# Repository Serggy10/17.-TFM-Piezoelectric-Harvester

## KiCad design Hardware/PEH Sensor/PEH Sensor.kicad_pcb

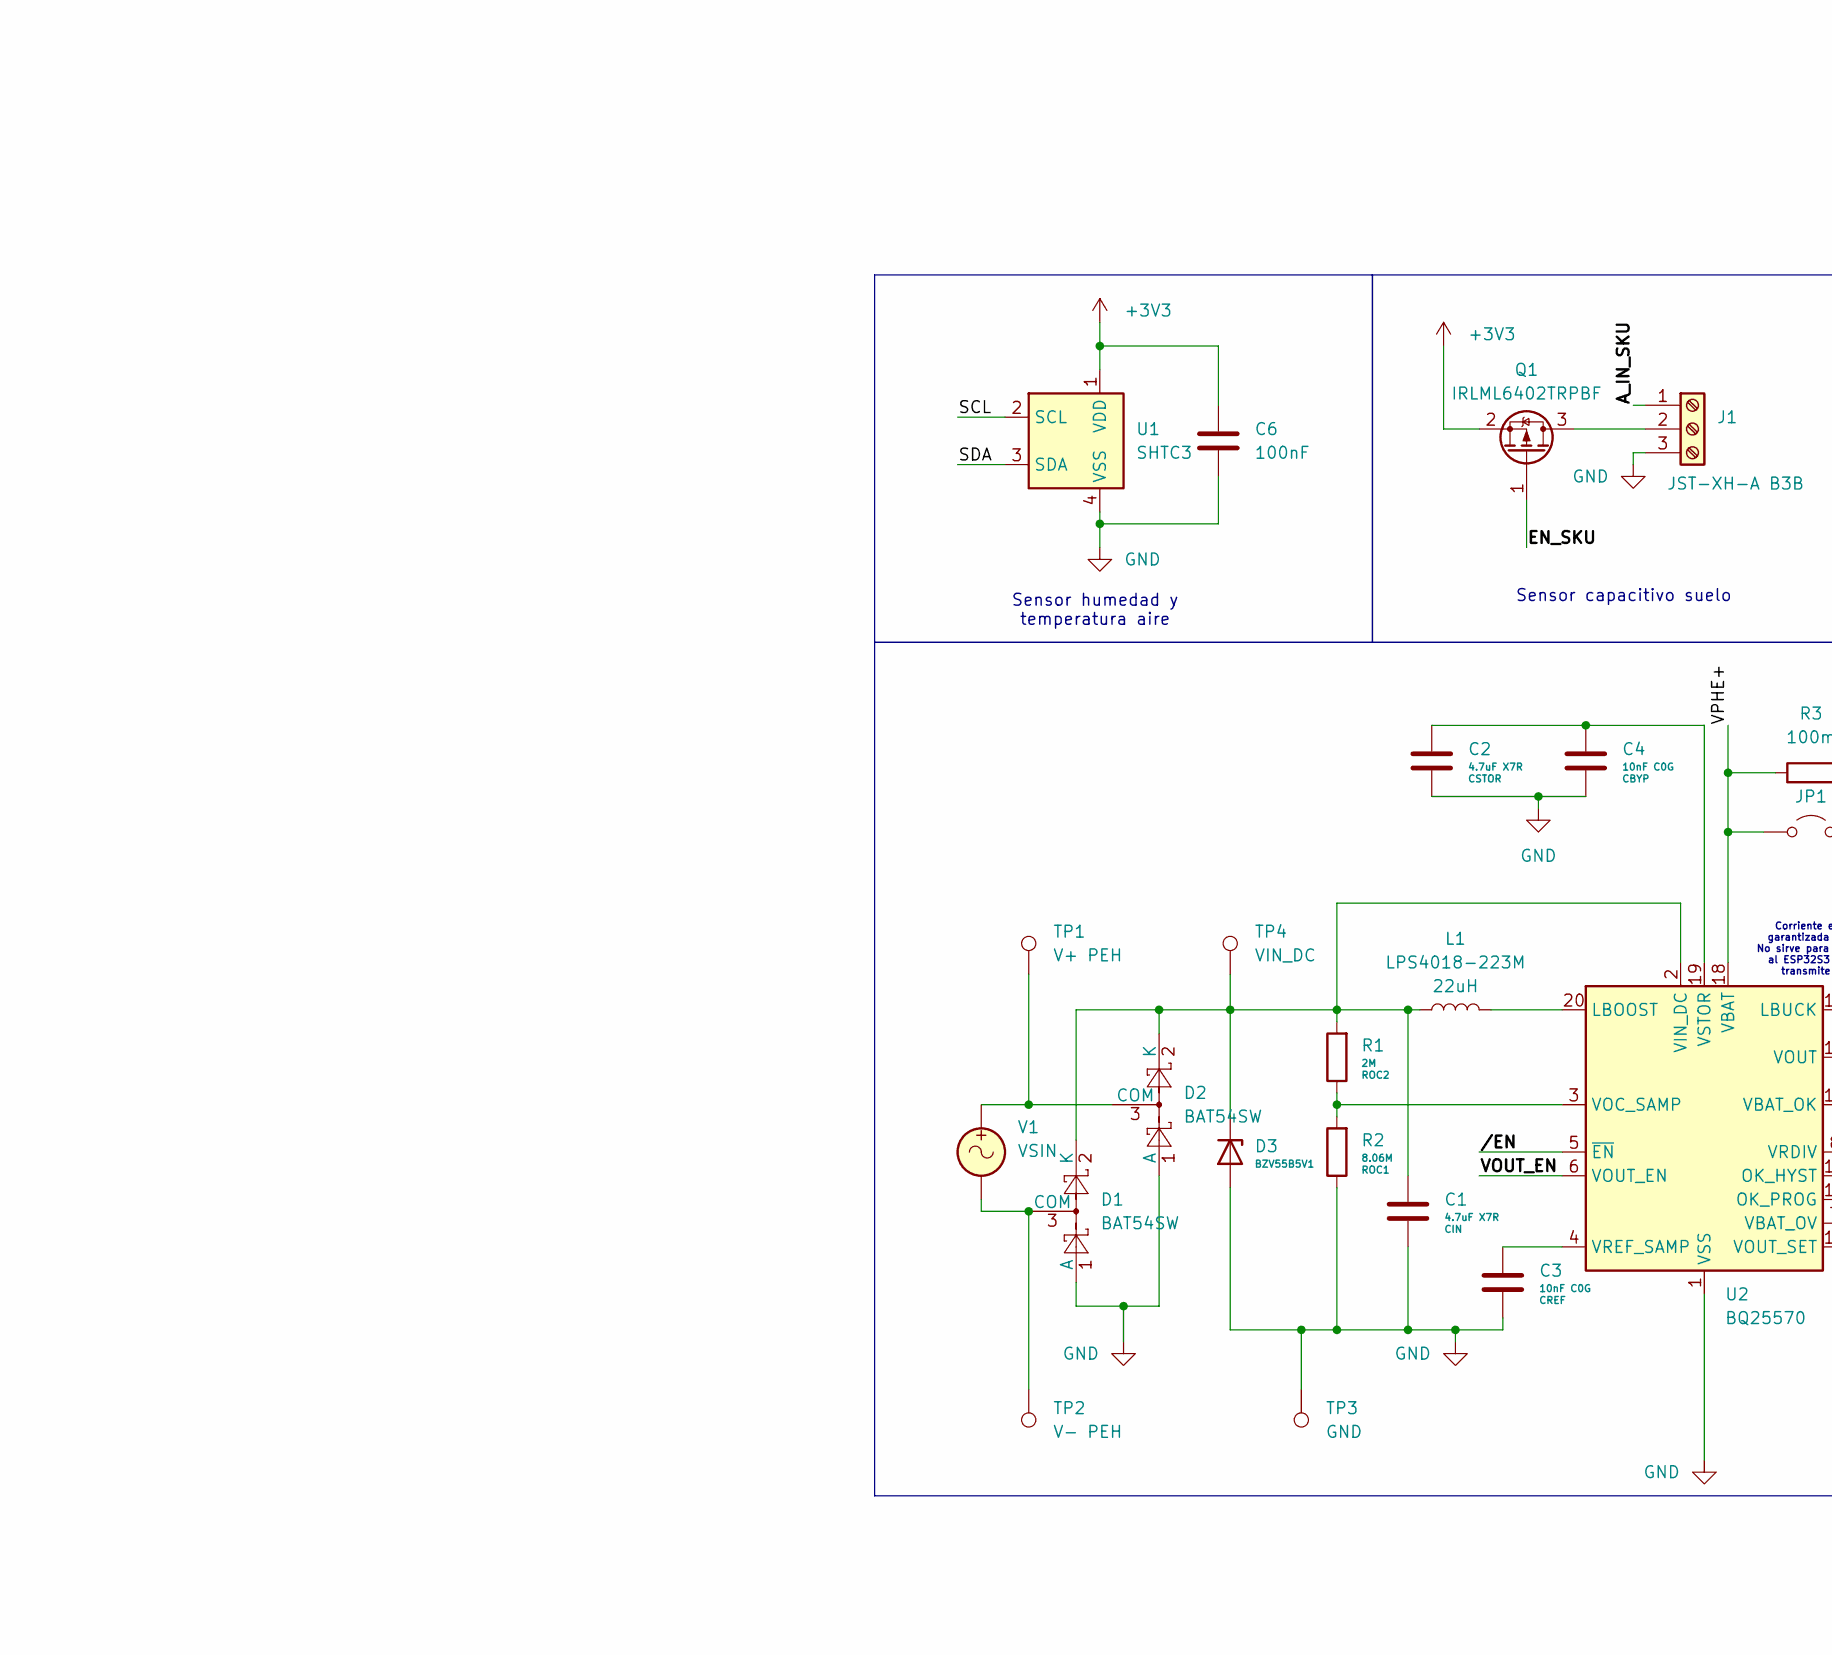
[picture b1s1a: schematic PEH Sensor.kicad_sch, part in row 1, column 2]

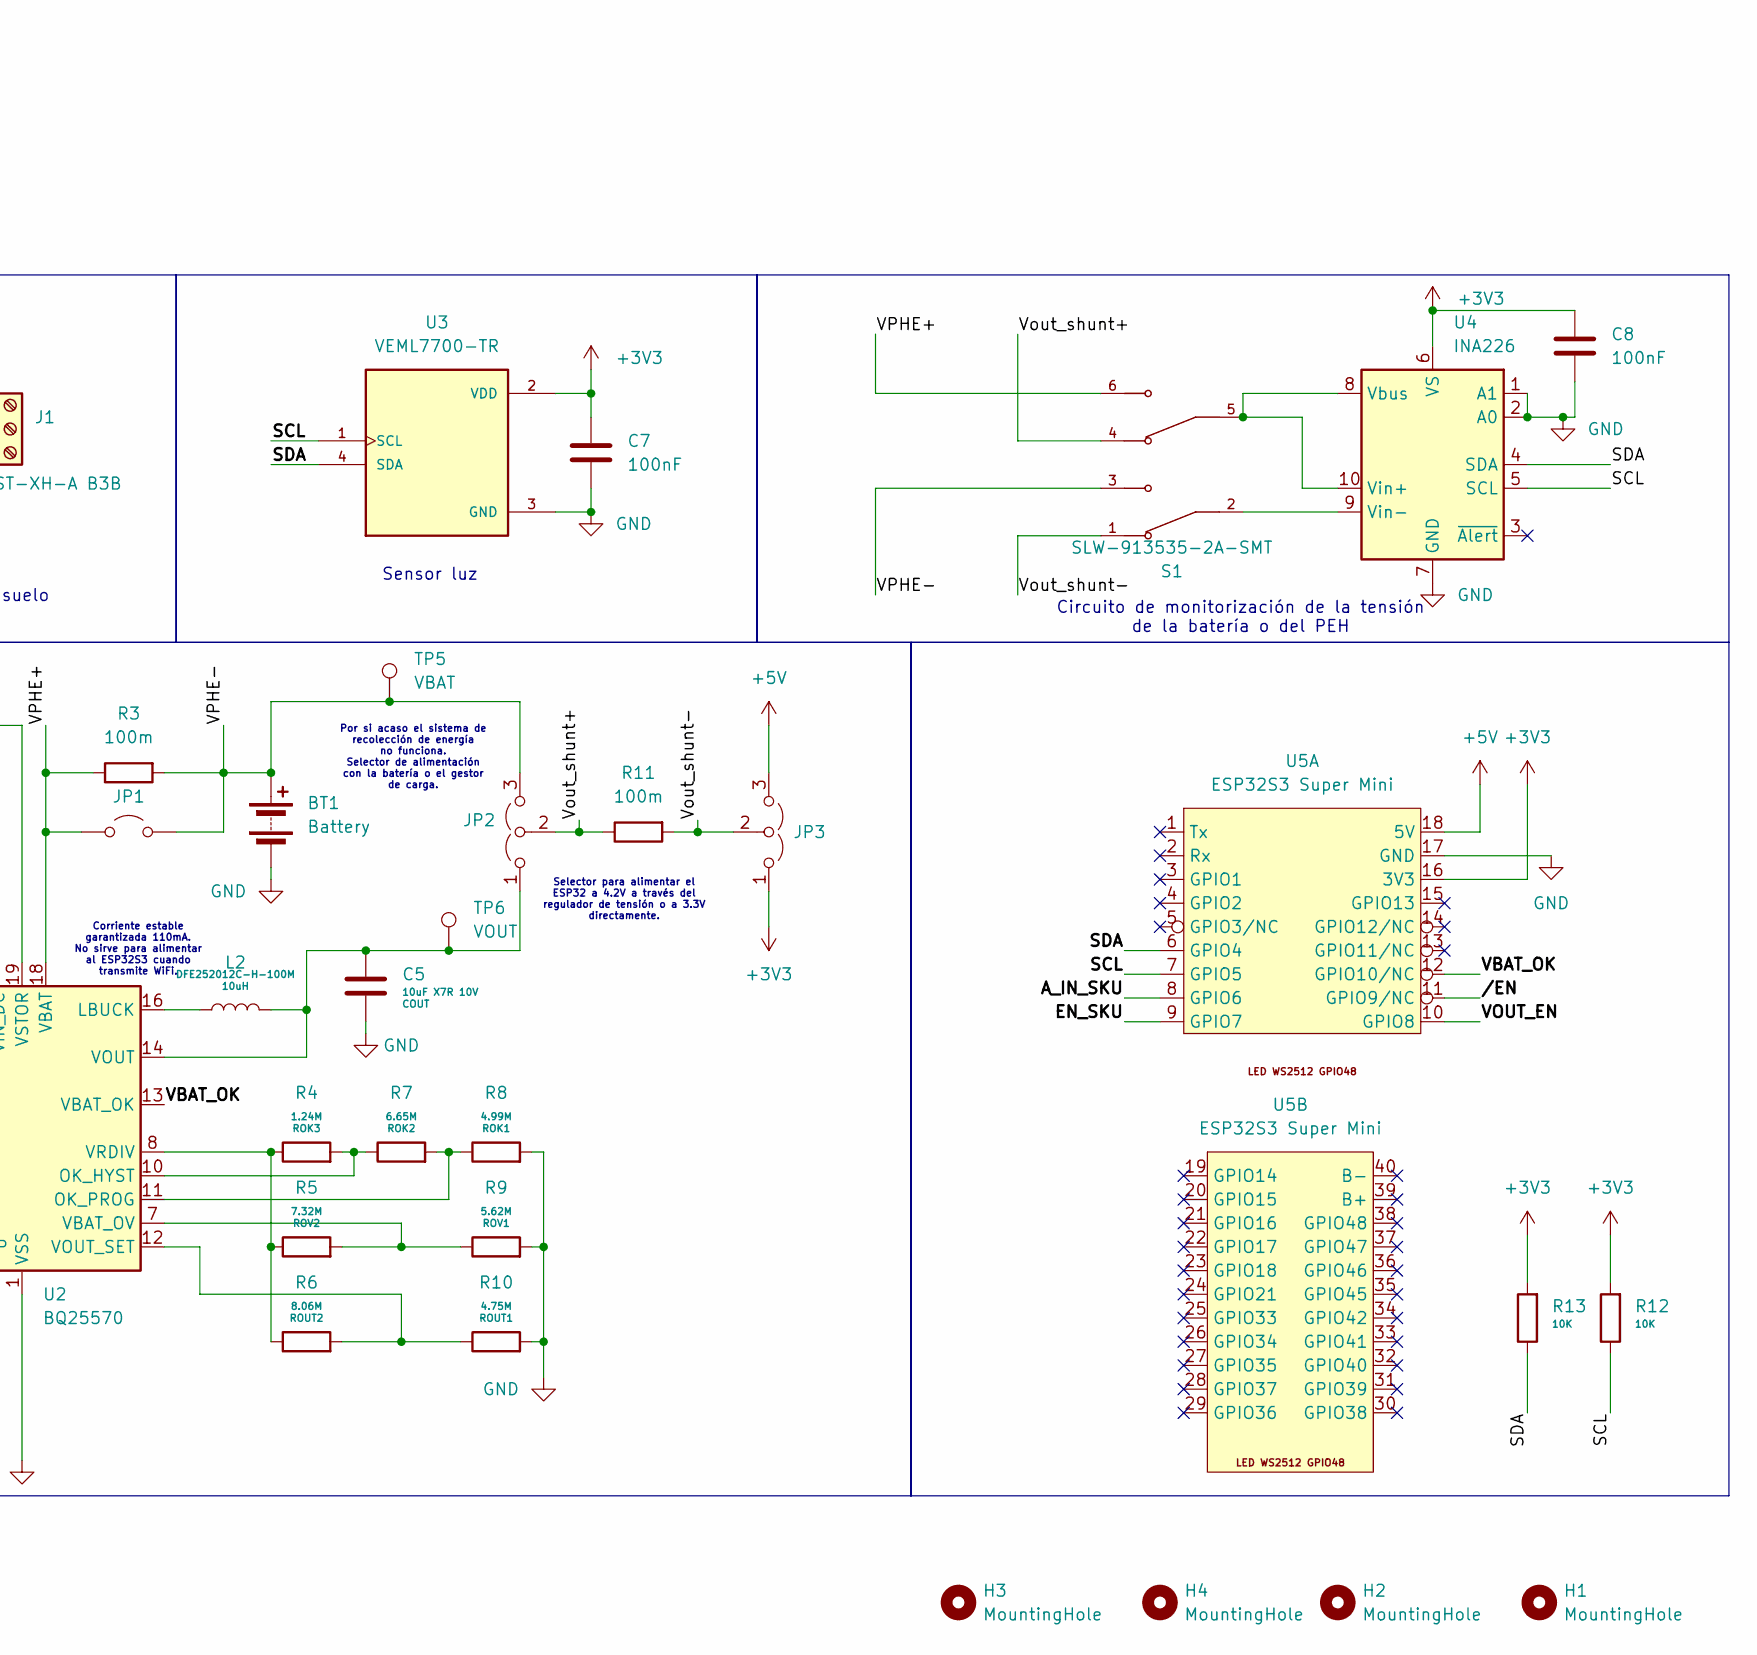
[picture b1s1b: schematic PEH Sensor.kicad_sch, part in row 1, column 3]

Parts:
BT1: Battery; JST_XH_B2B-XH-A_1x02_P2.50mm_Vertical
C1, C2: 4.7uF X7R; C_0805_2012Metric_Pad1.18x1.45mm_HandSolder
C3, C4: 10nF C0G; C_0805_2012Metric_Pad1.18x1.45mm_HandSolder
C5: 10uF X7R 10V; C_0805_2012Metric_Pad1.18x1.45mm_HandSolder
C6, C7, C8: 100nF; C_0805_2012Metric_Pad1.18x1.45mm_HandSolder
D1, D2: BAT54SW; SOT-323_SC-70
D3: BZV55B5V1; D_MiniMELF
H1, H2, H3, H4: MountingHole; MountingHole_3.2mm_M3_DIN965
J1: JST-XH-A B3B; JST_XH_B3B-XH-A_1x03_P2.50mm_Vertical
JP1: Jumper_2_Open; SolderJumper-2_P1.3mm_Open_Pad1.0x1.5mm
JP2, JP3: Jumper_3_Open; SolderJumper-3_P1.3mm_Open_Pad1.0x1.5mm_NumberLabels
L1: LPS4018-223M; L_Coilcraft_LPS4018
L2: DFE252012C-H-100M; L_1008_2520Metric_Pad1.43x2.20mm_HandSolder
Q1: IRLML6402TRPBF; SOT-23
R1: 2M; R_0805_2012Metric_Pad1.20x1.40mm_HandSolder
R2, R6: 8.06M; R_0805_2012Metric_Pad1.20x1.40mm_HandSolder
R3, R11: 100m; R_0805_2012Metric_Pad1.20x1.40mm_HandSolder
R4: 1.24M; R_0805_2012Metric_Pad1.20x1.40mm_HandSolder
R5: 7.32M; R_0805_2012Metric_Pad1.20x1.40mm_HandSolder
R7: 6.65M; R_0805_2012Metric_Pad1.20x1.40mm_HandSolder
R8: 4.99M; R_0805_2012Metric_Pad1.20x1.40mm_HandSolder
R9: 5.62M; R_0805_2012Metric_Pad1.20x1.40mm_HandSolder
R10: 4.75M; R_0805_2012Metric_Pad1.20x1.40mm_HandSolder
R12, R13: 10K; R_0805_2012Metric_Pad1.20x1.40mm_HandSolder
S1: SLW-913535-2A-SMT; SW_SLW-913535-2A-SMT; PARTREV 1.01
TP1: V+ PEH; TestPoint_Loop_D1.80mm_Drill1.0mm_Beaded
TP2: V- PEH; TestPoint_Loop_D1.80mm_Drill1.0mm_Beaded
TP3: GND; TestPoint_Loop_D1.80mm_Drill1.0mm_Beaded
TP4: VIN_DC; TestPoint_Loop_D1.80mm_Drill1.0mm_Beaded
TP5: VBAT; TestPoint_Loop_D1.80mm_Drill1.0mm_Beaded
TP6: VOUT; TestPoint_Loop_D1.80mm_Drill1.0mm_Beaded
U1: SHTC3; Sensirion_DFN-4-1EP_2x2mm_P1mm_EP0.7x1.6mm
U2: BQ25570; QFN-20-1EP_3.5x3.5mm_P0.5mm_EP2x2mm
U3: VEML7700-TR; XDCR_VEML7700-TR; PARTREV 1.6
U4: INA226; VSSOP-10_3x3mm_P0.5mm
U5: ESP32S3 Super Mini; ESP32 super mini
V1: VSIN; JST_XH_B2B-XH-A_1x02_P2.50mm_Vertical

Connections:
+3V3: C6.1, C7.1, C8.1, JP3.1 (A), Q1.2 (S), R12.2, R13.2, U1.1 (VDD), U3.2 (VDD), U4.6 (VS), U5.16 (3V3)
+5V: JP3.3 (B), U5.18 (5V)
/A_IN_SKU: J1.1, U5.8 (GPIO6)
/EN_SKU: Q1.1 (G), U5.9 (GPIO7)
/SCL: R12.1, U1.2 (SCL), U3.1 (SCL), U4.5 (SCL), U5.7 (GPIO5)
/SDA: R13.1, U1.3 (SDA), U3.4 (SDA), U4.4 (SDA), U5.6 (GPIO4)
/VBAT_OK: U2.13 (VBAT_OK), U5.12 (GPIO10/NC)
/VOUT_EN: U2.6 (VOUT_EN), U5.10 (GPIO8)
/VPHE+: JP1.1 (A), R3.1, S1.6, U2.18 (VBAT)
/VPHE-: BT1.1 (+), JP1.2 (B), JP2.3 (B), R3.2, S1.3, TP5.1
/Vout_shunt+: JP2.2 (C), R11.1, S1.4
/Vout_shunt-: JP3.2 (C), R11.2, S1.1
//EN: U2.5 (~EN), U5.11 (GPIO9/NC)
GND: BT1.2 (-), C1.2, C2.2, C3.2, C4.2, C5.2, C6.2, C7.2, C8.2, D1.1 (A), D2.1 (A), D3.2 (A), J1.3, R2.1, R8.2, R9.2, R10.2, TP3.1, U1.4 (VSS), U2.1 (VSS), U2.9 (VSS), U2.15 (VSS), U2.17 (VSS), U2.21 (VSS), U3.3 (GND), U4.1 (A1), U4.2 (A0), U4.7 (GND), U5.17 (GND)
unnamed: D1.3 (COM), TP2.1, V1.2
unnamed: C1.1, D1.2 (K), D2.2 (K), D3.1 (K), L1.1, R1.2, TP4.1, U2.2 (VIN_DC)
unnamed: D2.3 (COM), TP1.1, V1.1
unnamed: J1.2, Q1.3 (D)
unnamed: C5.1, JP2.1 (A), L2.2, TP6.1, U2.14 (VOUT)
unnamed: L1.2, U2.20 (LBOOST)
unnamed: L2.1, U2.16 (LBUCK)
unnamed: R4.2, R7.1, U2.10 (OK_HYST)
unnamed: R7.2, R8.1, U2.11 (OK_PROG)
unnamed: R5.2, R9.1, U2.7 (VBAT_OV)
unnamed: R1.1, R2.2, U2.3 (VOC_SAMP)
unnamed: R6.2, R10.1, U2.12 (VOUT_SET)
unnamed: R4.1, R5.1, R6.1, U2.8 (VRDIV)
unnamed: C3.1, U2.4 (VREF_SAMP)
unnamed: C2.1, C4.1, U2.19 (VSTOR)
unnamed: S1.5, U4.8 (Vbus), U4.10 (Vin+)
unnamed: S1.2, U4.9 (Vin-)

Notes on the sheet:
Corriente estable garantizada 110mA. No sirve para alimentar al ESP32S3 cuando transmite WiFi.
Sensor capacitivo suelo
Sensor luz
Circuito de monitorización de la tensión de la batería o del PEH
Por si acaso el sistema de recolección de energía no funciona. Selector de alimentación con la batería o el gestor de carga.
Sensor humedad y temperatura aire
Para superar el cold sart el PEH debe suministrar una potencia para mantener la carga continua.
Selector para alimentar el ESP32 a 4.2V a través del regulador de tensión o a 3.3V directamente.

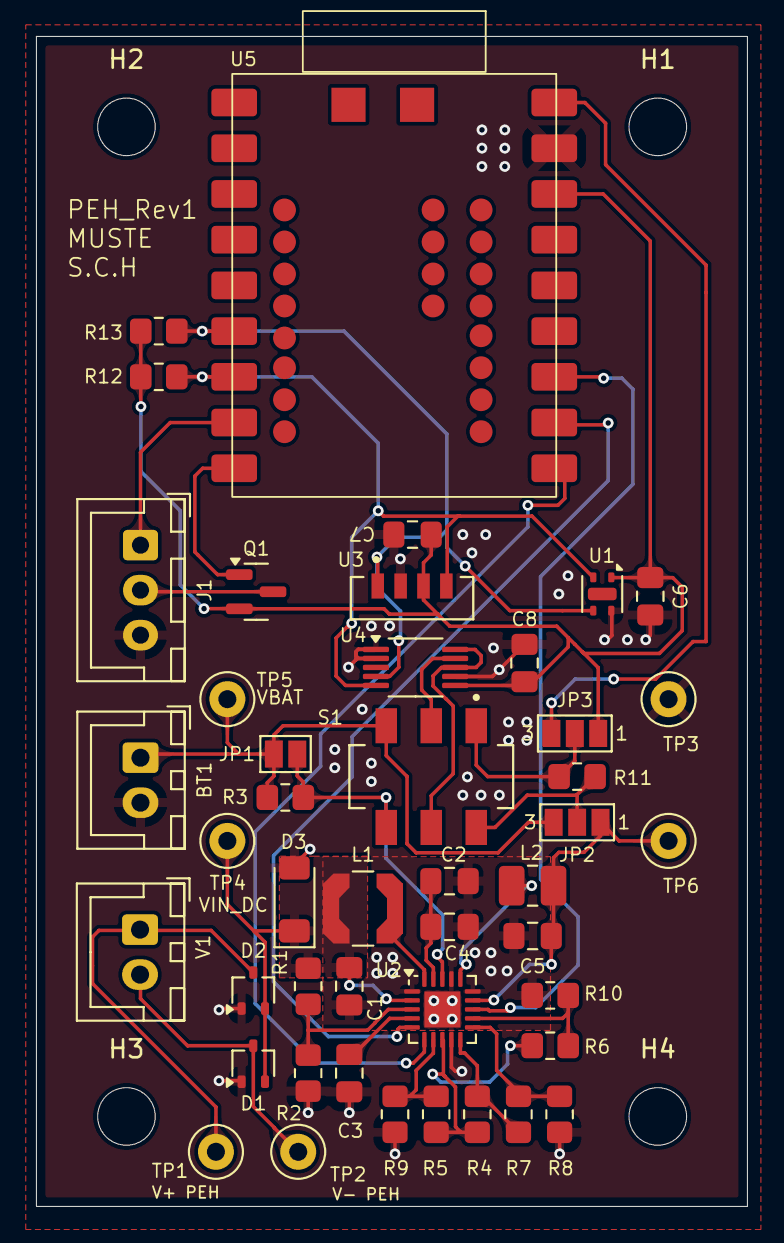
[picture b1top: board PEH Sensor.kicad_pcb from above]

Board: 2 copper layers, 39.5 x 65.0 mm, 49 parts (0 on the bottom side), 31 nets.

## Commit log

2025-06-01 Init commit
2025-06-01 Serial monitor working on ESP32-s3 super mini
2025-06-07 Several PCB updates to hardware. Started BLE app on androidstudio.
2025-06-07 App runing and ESP32 advertising every moment.
2025-06-07 Sending 10 sensor data in 2 packets of 5. Lag in transmision due to the 5 characterisitics.
2025-06-08 Sending 2 pakckets of 25 data (5 of each sensor).
2025-06-08 Updated ESP32 program with deepsleep.
2025-06-25 Programa de prueba de sensores y actualización de PCB con cambio en la librería del VEML770
2025-06-27 Included all the sensors readings and transmision with BLE.
2025-06-27 Changes made before including deeepsleep-lightsleep selection command.
2025-06-28 Data saved in SPIFFS. Icon and name changed in App.
2025-06-29 Added a luminous signal to distinguish between data acquisition, BLE advertising and light/deep sleep mode. A refresh mode with lightsleep has been added to prevent getting stuck when leaving deep sl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
